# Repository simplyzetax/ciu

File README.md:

# Central intelligence unit

## End goal: ESP32 that is Sena and Cardo Mesh compatible. Replaces Sena completely. Also, built in HUD inside of Goggles.

### Status

The Sena Mesh 3 air protocol has been recovered from firmware by static analysis: frame format, packet subtypes, discovery and admission, routing, timing, audio packing, and the protected-record crypto.

- [Mesh protocol static analysis](reports/sena-30k-mesh-protocol-static-analysis-2026-09-08.md) — current reference, including the ESP32-C6 implementation requirements and the over-the-air capture plan.
- [First-pass ESP32 feasibility](reports/sena-30k-mesh-3-firmware-esp32-feasibility.md) — superseded baseline, kept for the FCC and firmware-distribution evidence.
- `tools/mesh3.py` — clean-room reference implementation; `python3 tools/mesh3.py verify` re-derives every published vector from the local image.
- `firmware/` — downloaded images, extracted components, and `manifest.json` with verified hashes.

Open items are capture-dependent, not static: the lower MAC/FCS boundary, the exact Speex submode, and the predicted Group Mesh network-ID truncation.

### Development

Run `npm install` after cloning to install the Husky Git hooks. Before each
commit, the pre-commit hook runs `cargo check-esp` against every workspace
crate for the ESP32 target.

### Sena and Cardo replacement

Parts:

- [ESP32-C6](https://www.amazon.de/gp/product/B0GZTV9NDV/ref=ox_sc_act_title_1?smid=A2OYQMAUQB5NOO&psc=1)
- [500 mAh Akku](https://www.amazon.de/EEMB-500mAh-562438-JST2-0-Stecker-St%C3%BCck-blau/dp/B09DPPMX14)

### Goggles HUD

Parts:

- [0.96" OLED Display I2C/IIC/TWI 128x64 Pixel für Arduino](https://www.roboter-bausatz.de/p/0.96-oled-display-i2c-iic-twi-128x64-pixel-fuer-arduino)
- [Optical Prism 45° Splitting Ratio 50%:50%](https://www.amazon.de/gp/product/B0F7LHQWTG/ref=ox_sc_act_title_3?smid=A3FMVC8KTJNQWA&th=1)

INFO:

Serial 10 = Goggles
Serial 210 = Helmet

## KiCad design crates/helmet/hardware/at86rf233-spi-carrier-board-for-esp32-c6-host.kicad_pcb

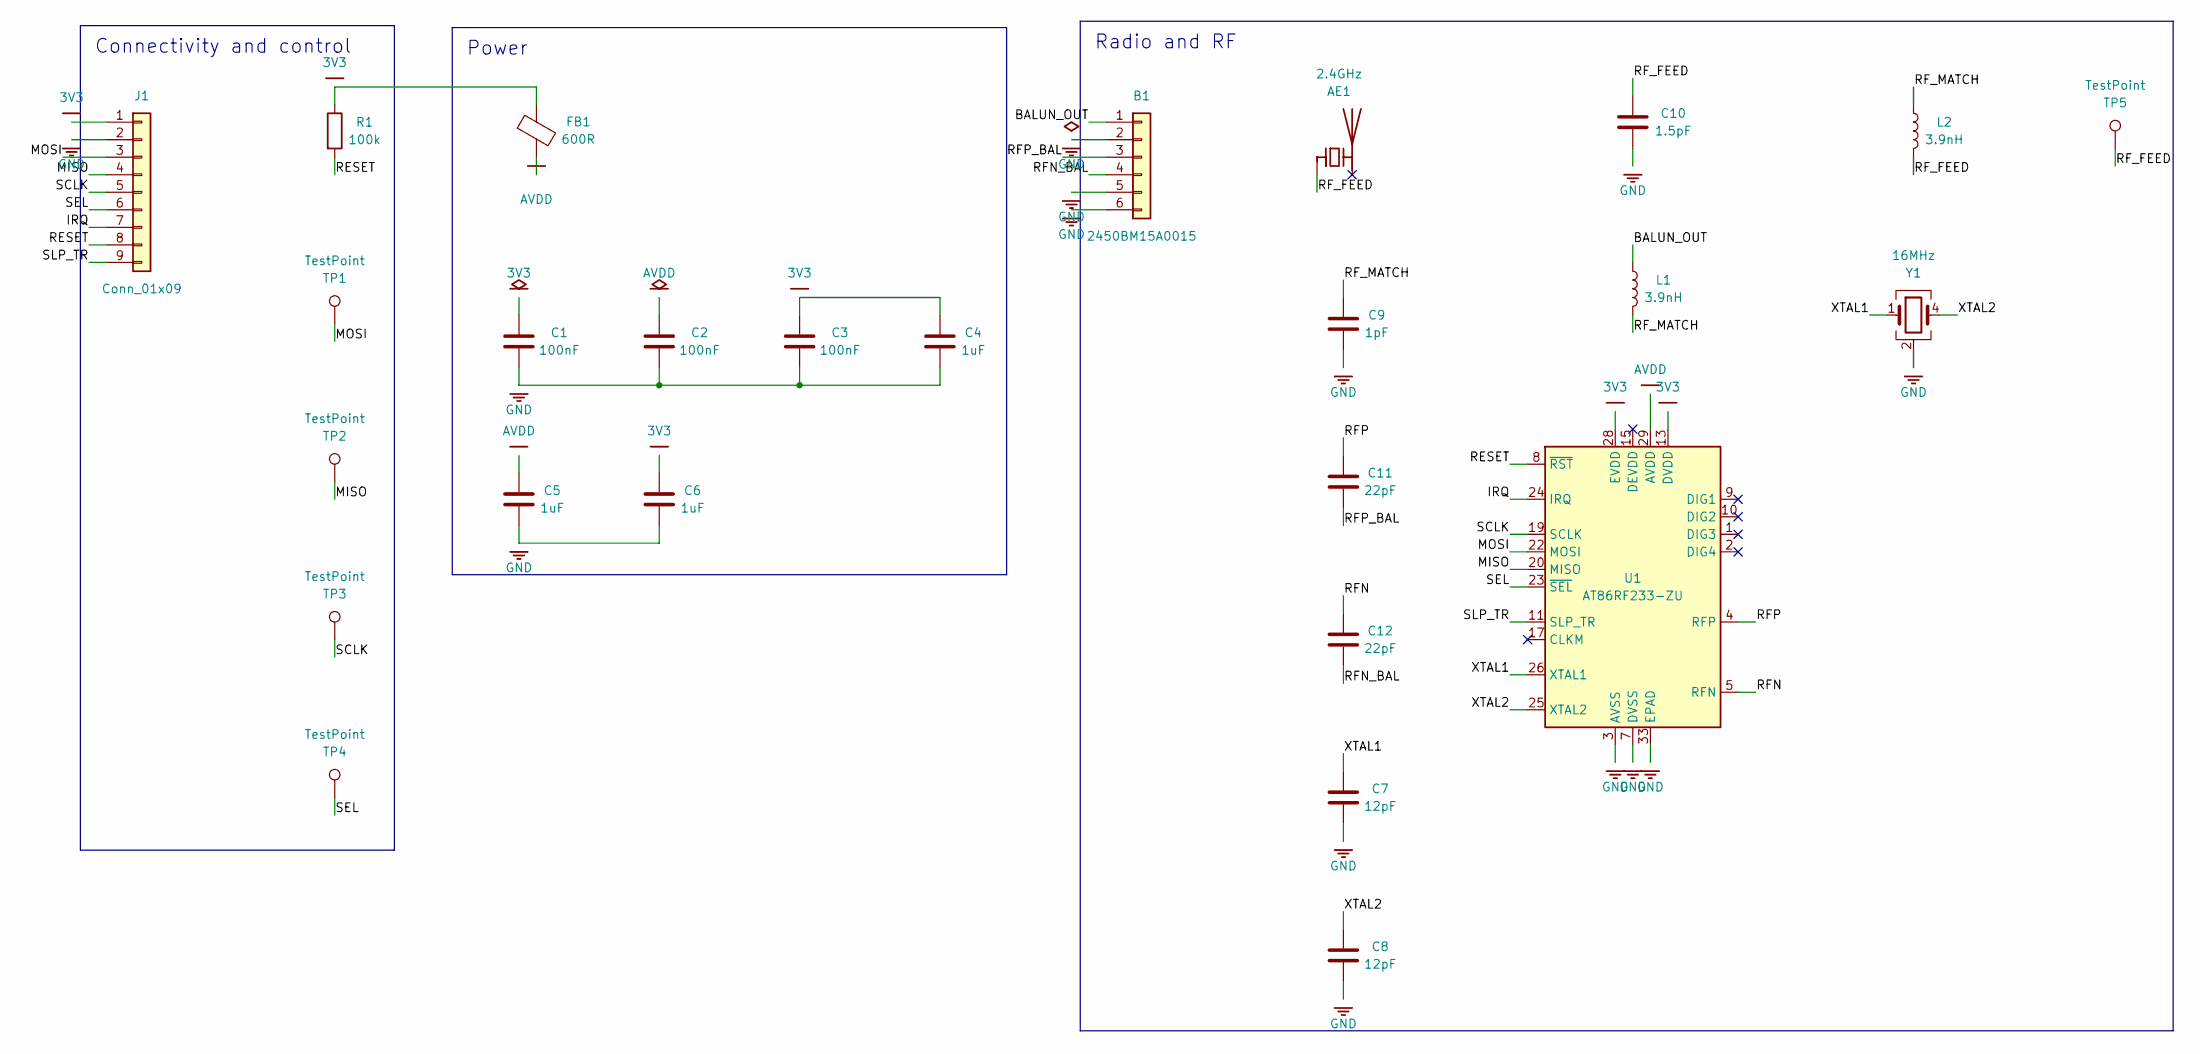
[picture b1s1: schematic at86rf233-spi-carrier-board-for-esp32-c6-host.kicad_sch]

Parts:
AE1: 2.4GHz; Johanson_2450AT18x100
B1: 2450BM15A0015; Johanson_2450BM15A0015
C1, C2, C3: 100nF; C_0402_1005Metric
C4, C5, C6: 1uF; C_0402_1005Metric
C7, C8: 12pF; C_0402_1005Metric
C9: 1pF; C_0402_1005Metric
C10: 1.5pF; C_0402_1005Metric
C11, C12: 22pF; C_0402_1005Metric
FB1: 600R; L_0402_1005Metric
J1: Conn_01x09; PinHeader_1x09_P2.54mm_Vertical
L1, L2: 3.9nH; L_0402_1005Metric
R1: 100k; R_0402_1005Metric
TP1, TP2, TP3, TP4, TP5: TestPoint; TestPoint_Keystone_5015_Micro_Mini
U1: AT86RF233-ZU; QFN-32-1EP_5x5mm_P0.5mm_EP3.3x3.3mm
Y1: 16MHz; Crystal_SMD_Abracon_ABM8G-4Pin_3.2x2.5mm

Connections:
3V3: C1.1, C3.1, C4.1, C6.1, FB1.1, J1.1, R1.1, U1.13 (DVDD), U1.14 (DVDD), U1.28 (EVDD)
/BALUN_OUT: B1.1, L1.1
/IRQ: J1.7, U1.24 (IRQ)
/MISO: J1.4, TP2.1 (1_1), U1.20 (MISO)
/MOSI: J1.3, TP1.1 (1_1), U1.22 (MOSI)
/RESET: J1.8, R1.2, U1.8 (~RST)
/RFN: C12.1, U1.5 (RFN)
/RFN_BAL: B1.4, C12.2
/RFP: C11.1, U1.4 (RFP)
/RFP_BAL: B1.3, C11.2
/RF_FEED: AE1.1 (FEED_1), C10.1, L2.2, TP5.1 (1_1)
/RF_MATCH: C9.1, L1.2, L2.1
/SCLK: J1.5, TP3.1 (1_1), U1.19 (SCLK)
/SEL: J1.6, TP4.1 (1_1), U1.23 (~SEL)
/SLP_TR: J1.9, U1.11 (SLP_TR)
/XTAL1: C7.1, U1.26 (XTAL1), Y1.1
/XTAL2: C8.1, U1.25 (XTAL2), Y1.4
AVDD: C2.1, C5.1, FB1.2, U1.29 (AVDD)
GND: B1.2, B1.5, B1.6, C1.2, C2.2, C3.2, C4.2, C5.2, C6.2, C7.2, C8.2, C9.2, C10.2, J1.2, U1.3 (AVSS), U1.6 (AVSS), U1.7 (DVSS), U1.12 (DVSS), U1.16 (DVSS), U1.18 (DVSS), U1.21 (DVSS), U1.27 (AVSS), U1.30 (AVSS), U1.31 (AVSS), U1.32 (AVSS), U1.33 (EPAD), Y1.2 (G), Y1.3 (G)

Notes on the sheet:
Connectivity and control
Power
Radio and RF

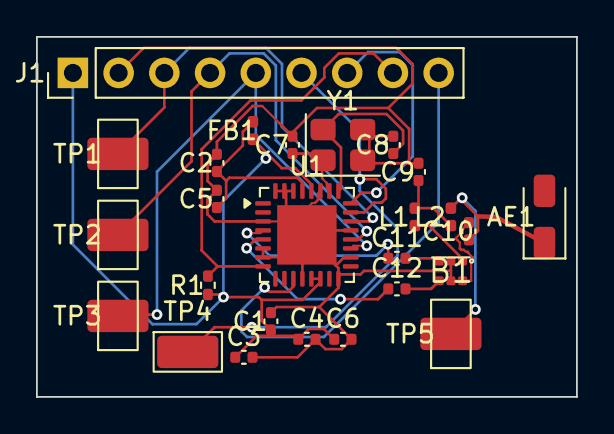
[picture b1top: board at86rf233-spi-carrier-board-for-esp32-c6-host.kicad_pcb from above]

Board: 2 copper layers, 30.0 x 20.0 mm, 26 parts (0 on the bottom side), 19 nets.

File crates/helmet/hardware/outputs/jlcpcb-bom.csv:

Comment,Designator,Footprint,LCSC Part #
2.4GHz,AE1,RF_Antenna:Johanson_2450AT18x100,
2450BM15A0015,B1,ciu:Johanson_2450BM15A0015,
100nF,"C1,C2,C3",Capacitor_SMD:C_0402_1005Metric,
1uF,"C4,C5,C6",Capacitor_SMD:C_0402_1005Metric,
12pF,"C7,C8",Capacitor_SMD:C_0402_1005Metric,
1pF,C9,Capacitor_SMD:C_0402_1005Metric,
1.5pF,C10,Capacitor_SMD:C_0402_1005Metric,
22pF,"C11,C12",Capacitor_SMD:C_0402_1005Metric,
600R,FB1,Inductor_SMD:L_0402_1005Metric,
Conn_01x09,J1,Connector_PinHeader_2.54mm:PinHeader_1x09_P2.54mm_Vertical,
3.9nH,"L1,L2",Inductor_SMD:L_0402_1005Metric,
100k,R1,Resistor_SMD:R_0402_1005Metric,
TestPoint,"TP1,TP2,TP3,TP4,TP5",TestPoint:TestPoint_Keystone_5015_Micro_Mini,
AT86RF233-ZU,U1,Package_DFN_QFN:QFN-32-1EP_5x5mm_P0.5mm_EP3.3x3.3mm,
16MHz,Y1,Crystal:Crystal_SMD_Abracon_ABM8G-4Pin_3.2x2.5mm,
